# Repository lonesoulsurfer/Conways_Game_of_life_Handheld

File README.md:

YouTube Vid
Short - https://youtube.com/shorts/Atr1aoWWVLA

Long - https://youtu.be/dLQRpCf72iw

I’ve been fascinated with Conway’s Game of Life ever since I read ‘The Recursive Universe’ way back in 2012. Since then, I wanted a way that I could play the game just like you would play a Nintendo ‘Game & Watch’ – a pocket-sized version that I could whip out anytime and start to explore & build my own patterns.

Fast-forward to 2025 and that idea has become reality! Arduino AI Assistant has been a massive help in building the code and there is absolutely no way that I could of done it without AI’s assistance. If you haven’t used it before and don’t know much about coding, then I strongly recommend that you give it a try.

So, what is Conway’s Game of Life (or GOL for short!). I recently gave the below description in another GOL project which might help those that haven’t heard of it before:

The Game of Life is a cellular automation created by mathematician John Conway. It's what is known as a zero player game, meaning that its evolution and game play is determined by its initial state and requires no further input. You interact with the Game of Life by creating an initial configuration and observing how it evolves.

The game itself is based on a few, simple, mathematical rules consisting of a grid of cells that can either live, die or multiply. When the game is run, the cells can give the illusion that they are alive which is what makes this game so interesting.
Now you know what it is – what does my hand held game version do?

Core Game

• Cellular Automaton: Simulates Conway's famous "zero-player game" where cells live/die based on neighbor count 
• Displayed on a 128x64 OLED screen 
• Toroidal World: Edges wrap around (top connects to bottom, left to right)

5 Game Modes (4 & 5 added in V2)
1. Random Game: Starts with random cell pattern, auto-resets when pattern dies/repeats
2. Custom Builder: Interactive editor to design your own starting patterns
3. Preset Patterns: 5 famous Conway patterns including Gosper Glider Gun
4. Custom Game: Build your own pattern with cursor, long-press SET to start
5. Alt Games: Alternative cellular automata collection
   
     • Brian's Brain: 3-state automaton with birth/dying/dead phases
   
     • Day & Night: Inverse Conway rules creating dense stable patterns
   
     • Seeds: Birth-only automaton creating explosive wave patterns
   
     • Langton's Ant: Single ant creating emergent highway patterns

Controls (5-button resistor ladder)

• Menu Navigation: UP/DOWN navigate, SET selects, LEFT goes back 
• Pattern Editor: Arrow keys move cursor, SET toggles cells, long-press SET starts simulation 
• During Simulation: UP/DOWN changes speed (12 levels), LEFT/RIGHT generates new random

Features

• Real-time Statistics: Generation counter, live cell count, max cells reached 
• Smart Detection: Automatically detects when patterns die out or start repeating 
• Game Over Screen: Shows final statistics for 4 seconds 
• Battery Optimized: Efficient bit-manipulation algorithms 
• Menu System: Clean interface with pattern submenu

Heres some more ideas to implement:

Pattern Management

• Pattern Save/Load: Store custom patterns in EEPROM with names 

• Pattern Library: More famous patterns (pulsar, pentadecathlon, etc.) 

• Random Seeds: Different randomization algorithms (sparse, dense, clusters) 

• Symmetrical Patterns: Generate symmetric starting conditions

Game Modes

• Survival Mode: Try to keep population above threshold for X generations 

• Target Mode: Reach specific cell count goals 

• Time Challenge: Fastest to stabilization 

• Multi-Rule Mode: Different cellular automaton rules (B36/S23, etc.)

Advanced Controls

• Step Mode: Advance one generation at a time with button press 

• Rewind: Store last N generations for backward stepping 

• Pause/Resume: Freeze simulation mid-run 

• Bookmark Positions: Mark interesting generations to return to

Statistics & Analysis

• Population Oscillation Detection: Identify period-N oscillators 

• Stability Analysis: Time to stabilization metrics 

• High Score System: Longest-lived patterns, highest populations 

• Pattern Classification: Auto-detect gliders, oscillators, still lifes

Hardware Enhancements

• Sound Effects: Beeps for births/deaths, musical tones for populations 

 • Color Coding: Different colors for cell age or generation born

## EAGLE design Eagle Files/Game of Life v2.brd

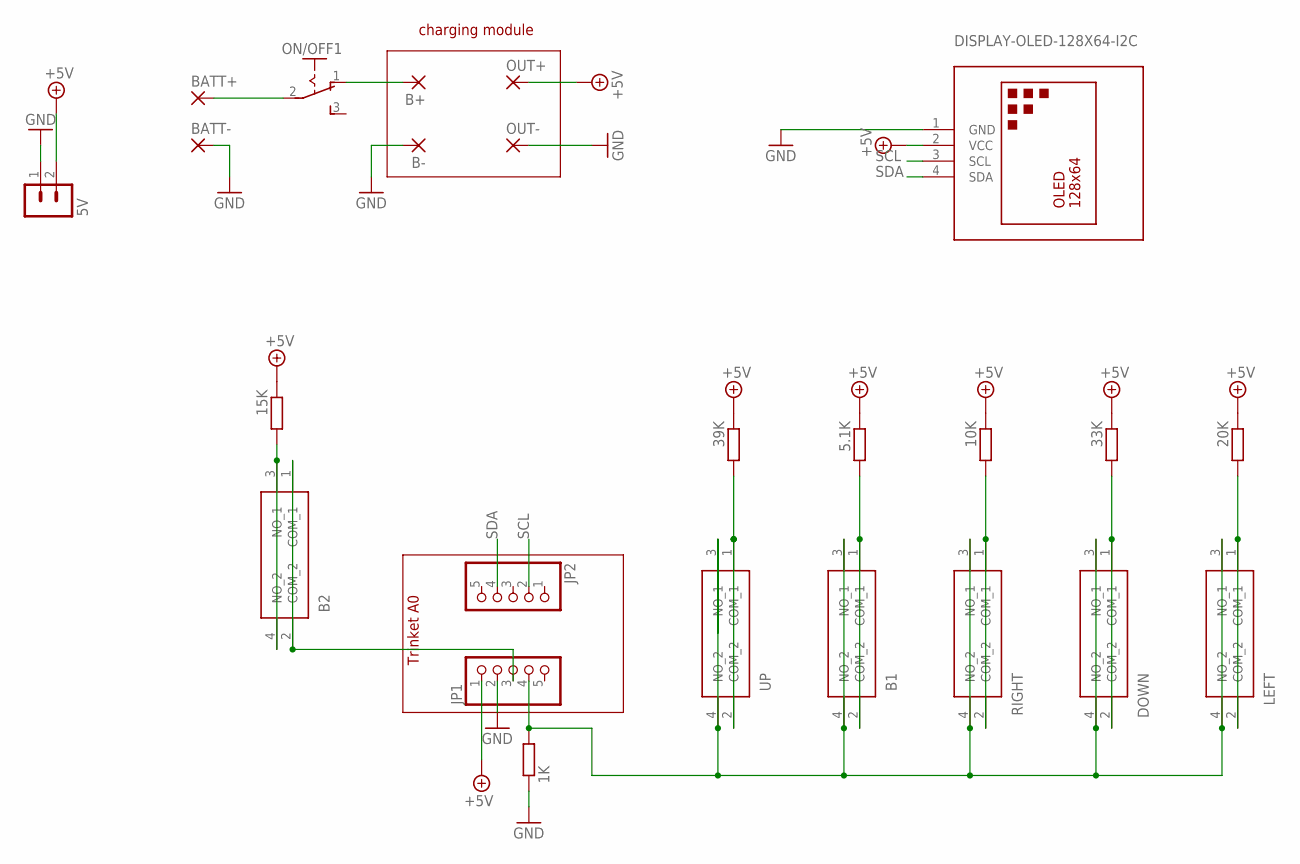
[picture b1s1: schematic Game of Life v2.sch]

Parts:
5V: B2B-PH-K-S
B1, B2: 101-0364-EV; 1010364EV
B+: SMD5; SMD2,54-5,08
B-: SMD5; SMD2,54-5,08
BATT+: SMD5; SMD2,54-5,08
BATT-: SMD5; SMD2,54-5,08
DOWN: 101-0364-EV; 1010364EV
JP1, JP2: PINHD-1X5; 1X05
LEFT: 101-0364-EV; 1010364EV
ON/OFF1: M251
OUT+: SMD5; SMD2,54-5,08
OUT-: SMD5; SMD2,54-5,08
R1: 1K; 0207/10
R2: 20K; 0207/10
R3: 39K; 0207/10
R4: 10K; 0207/10
R5: 33K; 0207/10
R6: 5.1K; 0207/10
R7: 15K; 0207/10
RIGHT: 101-0364-EV; 1010364EV
U$2: DISPLAY-OLED-128X64-I2C
UP: 101-0364-EV; 1010364EV

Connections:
+5V: 5V.2, JP1.1, OUT+.1, R2.1, R3.1, R4.1, R5.1, R6.1, R7.1, U$2.2 (VCC)
GND: 5V.1, B-.1, BATT-.1, JP1.2, OUT-.1, R1.1, U$2.1 (GND)
unnamed: DOWN.1 (COM_1), DOWN.2 (COM_2), R5.2
unnamed: R3.2, UP.1 (COM_1), UP.2 (COM_2)
unnamed: R4.2, RIGHT.1 (COM_1), RIGHT.2 (COM_2)
unnamed: B1.3 (NO_1), B1.4 (NO_2), DOWN.3 (NO_1), DOWN.4 (NO_2), JP1.4, LEFT.3 (NO_1), LEFT.4 (NO_2), R1.2, RIGHT.3 (NO_1), RIGHT.4 (NO_2), UP.3 (NO_1), UP.4 (NO_2)
unnamed: LEFT.1 (COM_1), LEFT.2 (COM_2), R2.2
unnamed: B1.1 (COM_1), B1.2 (COM_2), R6.2
unnamed: B2.1 (COM_1), B2.2 (COM_2), JP1.3
unnamed: BATT+.1, ON/OFF1.2
unnamed: B+.1, ON/OFF1.1 (O)
unnamed: B2.3 (NO_1), B2.4 (NO_2), R7.2
SCL: JP2.2, U$2.3 (SCL)
SDA: JP2.4, U$2.4 (SDA)

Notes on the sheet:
Trinket A0
charging module

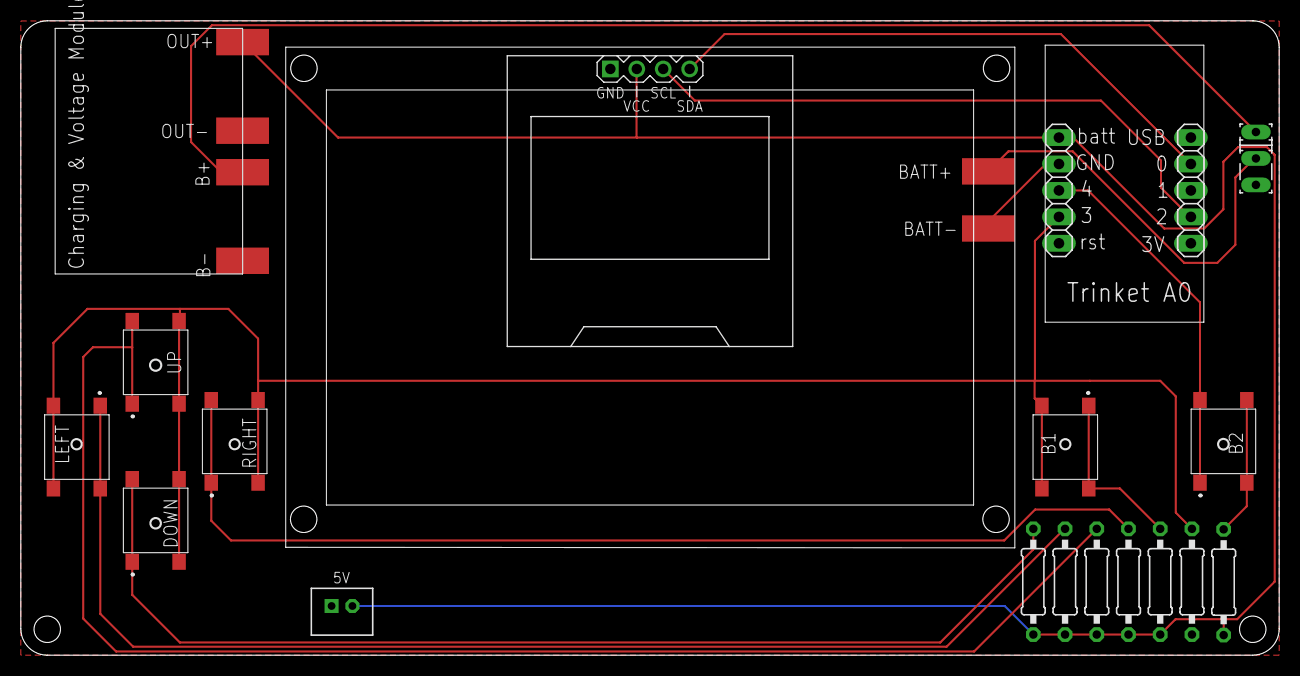
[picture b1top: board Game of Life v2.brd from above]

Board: 2 copper layers, 120.9 x 60.9 mm, 24 parts (0 on the bottom side), 14 nets.

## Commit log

2025-09-25 Add files via upload
    V1 is the original game based on Conways Game of Life
    V2 updates include:
    Symmetric Game: Generate symmetric patterns (Small/Medium/Large)
    Alt Games: Alternative cellular automata collection
    • Brian's Brain: 3-state automaton with birth/dying/dead phases
    • Day & Night: Inverse Conway rules creating dense stable patterns

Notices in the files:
parts and their libraries:
diy-modules: Released under the Creative Commons Attribution 4.0 International License: http://creativecommons.org/licenses/by/4.0
